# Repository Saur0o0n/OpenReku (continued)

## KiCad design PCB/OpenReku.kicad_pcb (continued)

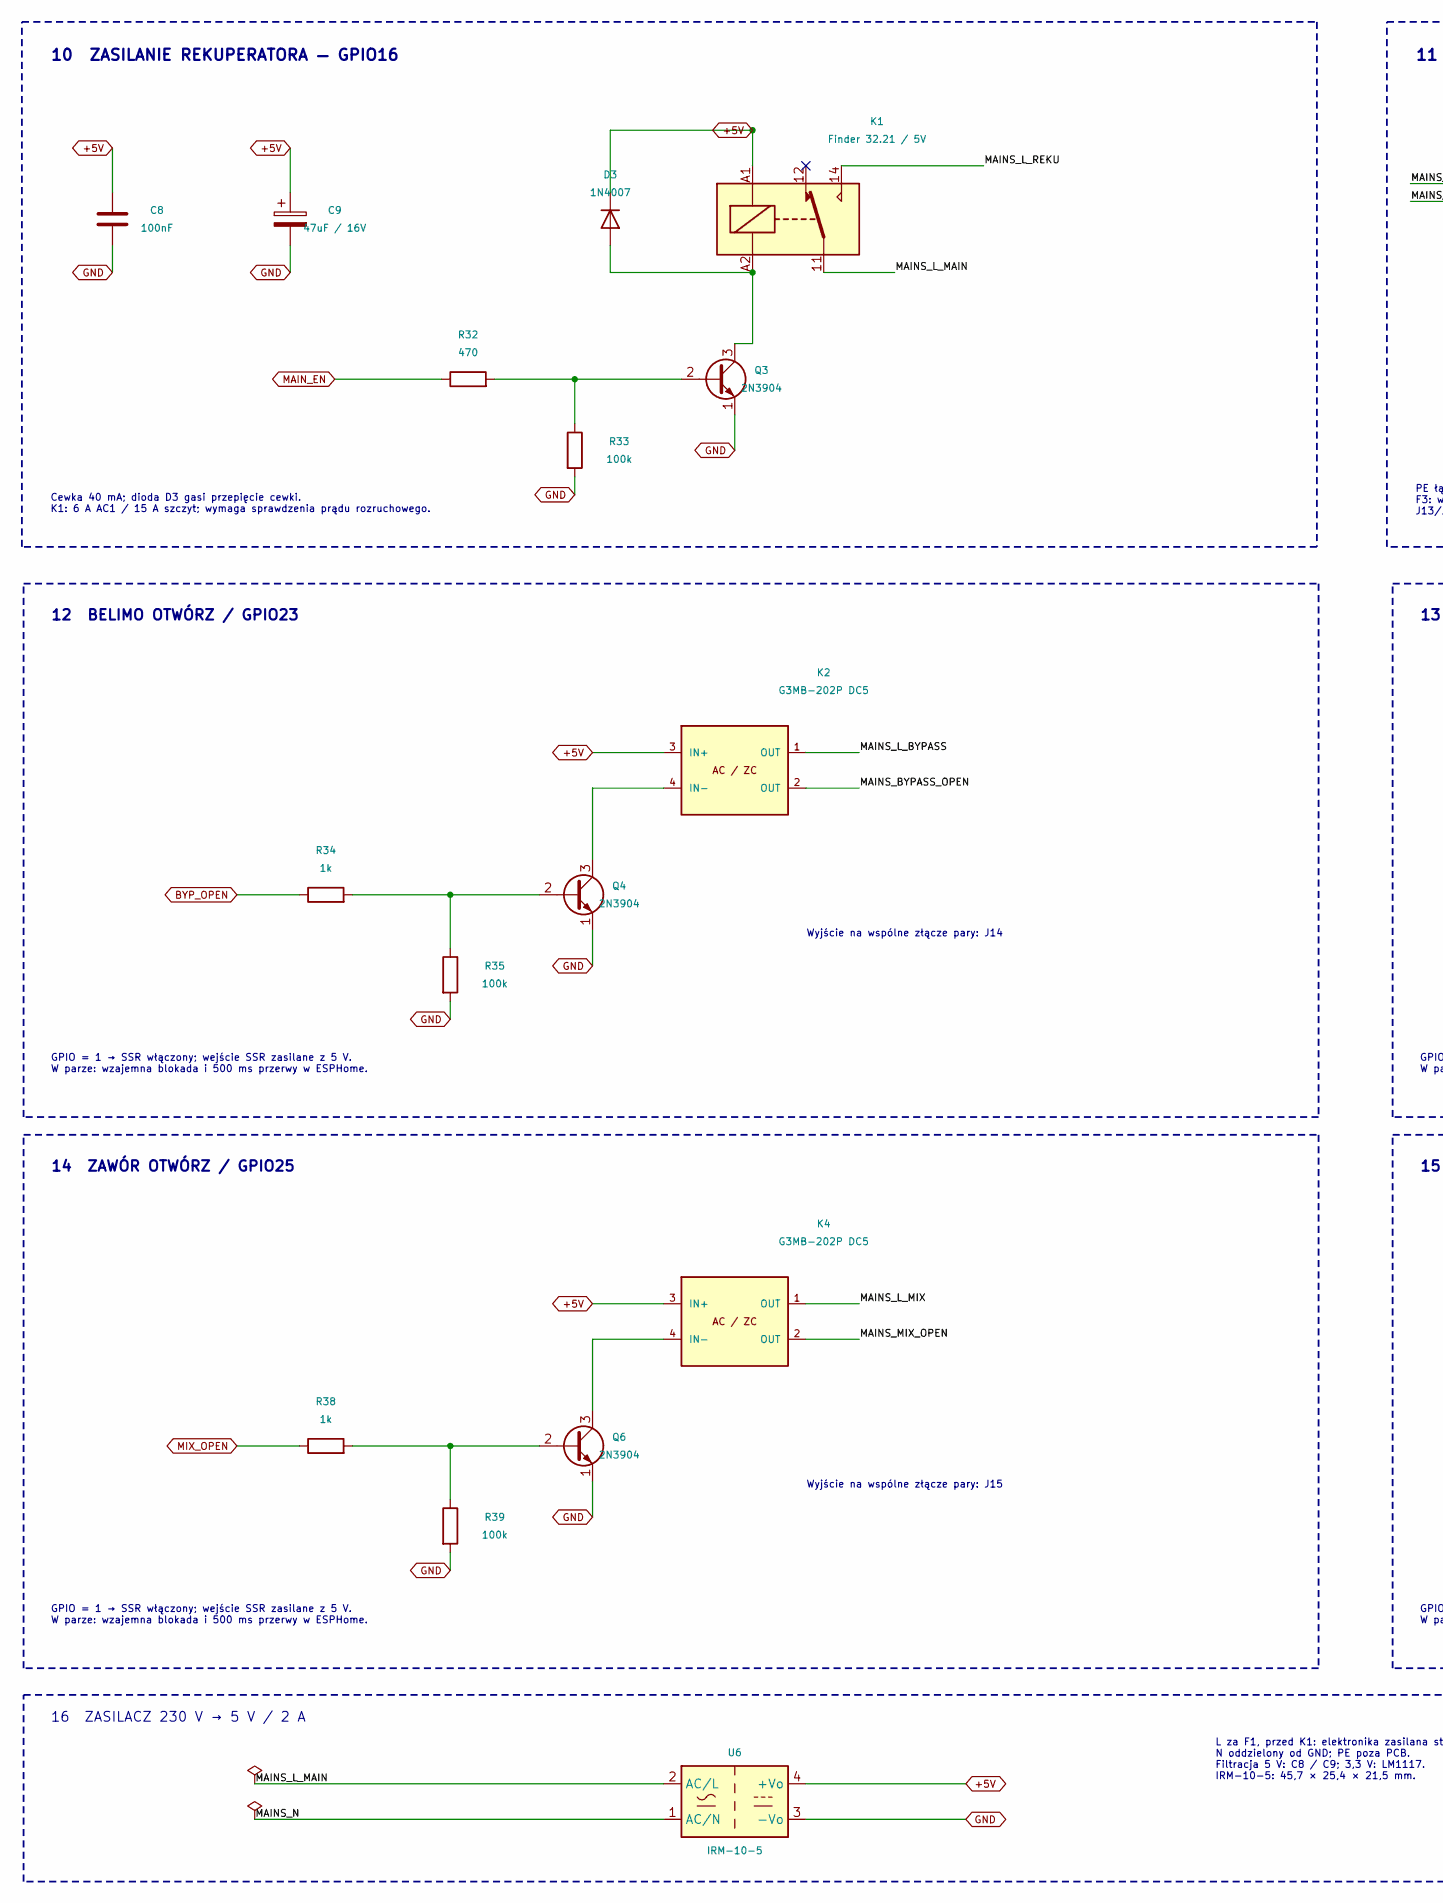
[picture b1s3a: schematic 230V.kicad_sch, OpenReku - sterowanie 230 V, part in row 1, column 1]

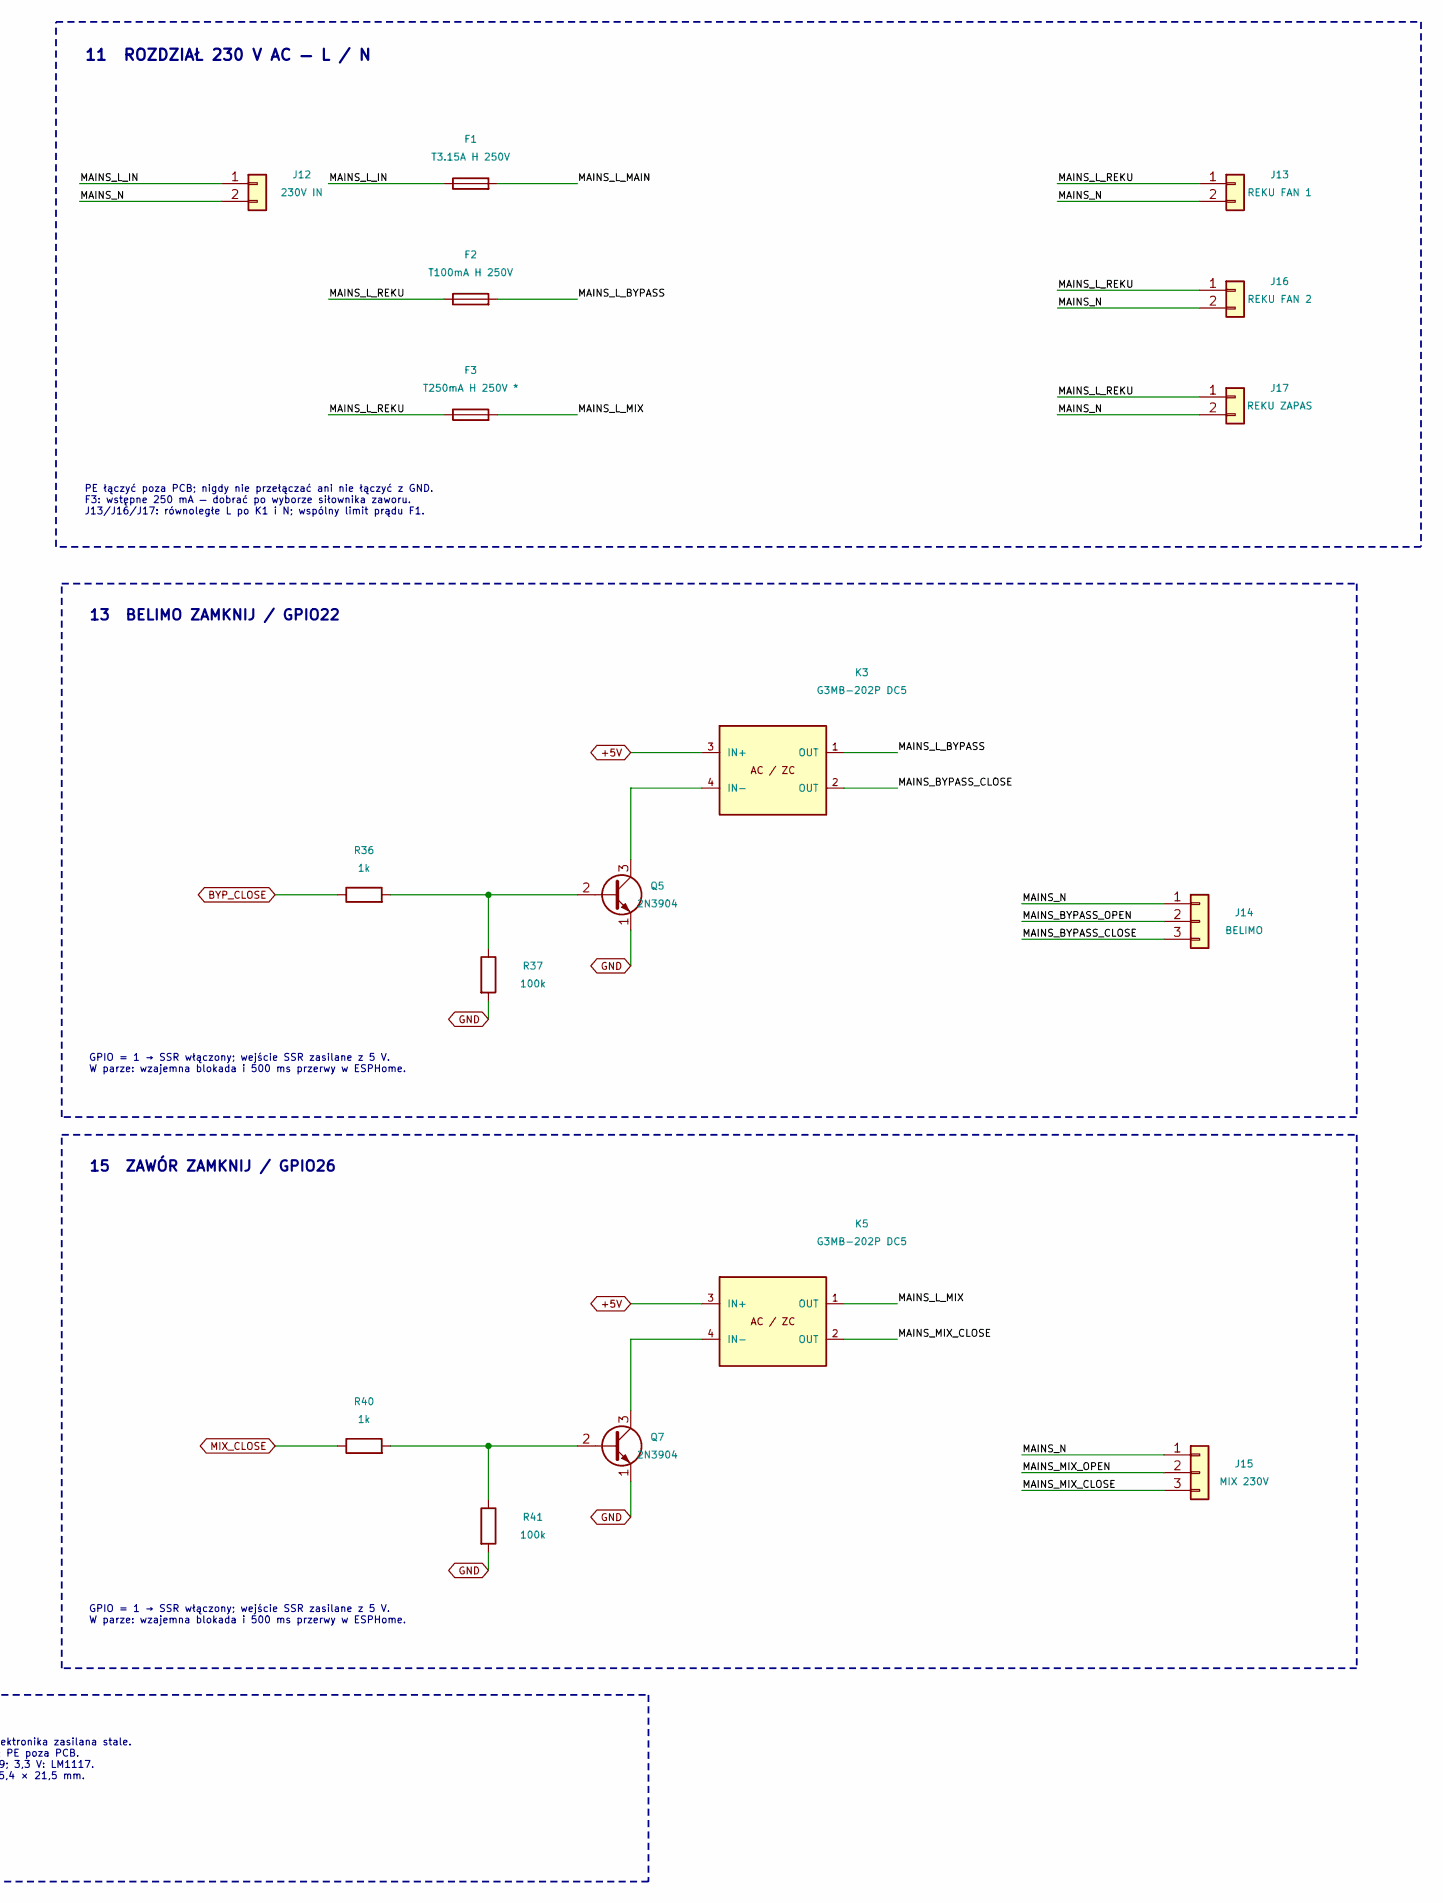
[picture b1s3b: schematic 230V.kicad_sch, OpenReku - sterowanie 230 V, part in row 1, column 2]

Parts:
C8: 100nF; C_1206_3216Metric
C9: 47uF / 16V; CP_Radial_D5.0mm_P2.00mm
D3: 1N4007; D_DO-41_SOD81_P10.16mm_Horizontal
F1: T3.15A H 250V; Fuseholder_Cylinder-5x20mm_Schurter_0031_8201_Horizontal_Op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
F2: T100mA H 250V; Fuseholder_Cylinder-5x20mm_Schurter_0031_8201_Horizontal_Op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
F3: T250mA H 250V *; Fuseholder_Cylinder-5x20mm_Schurter_0031_8201_Horizontal_Op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
J12: 230V IN; PhoenixContact_MSTBA_2,5_2-G-5,08_1x02_P5.08mm_Horizontal_E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; MPN 1757242
J13: REKU FAN 1; PhoenixContact_MSTBA_2,5_2-G-5,08_1x02_P5.08mm_Horizontal_E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; MPN 1757242
J14: BELIMO; PhoenixContact_MSTBA_2,5_3-G-5,08_1x03_P5.08mm_Horizontal_E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; MPN 1757255
J15: MIX 230V; PhoenixContact_MSTBA_2,5_3-G-5,08_1x03_P5.08mm_Horizontal_E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; MPN 1757255
J16: REKU FAN 2; PhoenixContact_MSTBA_2,5_2-G-5,08_1x02_P5.08mm_Horizontal_E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; MPN 1757242
J17: REKU ZAPAS; PhoenixContact_MSTBA_2,5_2-G-5,08_1x02_P5.08mm_Horizontal_E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; MPN 1757242
K1: Finder 32.21 / 5V; Relay_SPDT_Finder_32.21-x000; MPN 32.21.7.005.4000
K2, K3, K4, K5: G3MB-202P DC5; Omron_G3MB-202P_SIP4; MPN G3MB-202P DC5
Q3, Q4, Q5, Q6, Q7: 2N3904; TO-92_Inline
R32: 470; R_1206_3216Metric
R33, R35, R37, R39, R41: 100k; R_1206_3216Metric
R34, R36, R38, R40: 1k; R_1206_3216Metric
U6: IRM-10-5; Converter_ACDC_MeanWell_IRM-10-xx_THT

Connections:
+5V: C8.1, C9.1, D3.1 (K), K1.A1, K2.3 (IN+), K3.3 (IN+), K4.3 (IN+), K5.3 (IN+), U6.4 (+Vo); also elsewhere on the board
/230V/MAINS_BYPASS_CLOSE: J14.3, K3.2 (OUT)
/230V/MAINS_BYPASS_OPEN: J14.2, K2.2 (OUT)
/230V/MAINS_L_BYPASS: F2.2, K2.1 (OUT), K3.1 (OUT)
/230V/MAINS_L_IN: F1.1, J12.1
/230V/MAINS_L_MAIN: F1.2, K1.11, U6.2 (AC/L)
/230V/MAINS_L_MIX: F3.2, K4.1 (OUT), K5.1 (OUT)
/230V/MAINS_L_REKU: F2.1, F3.1, J13.1, J16.1, J17.1, K1.14
/230V/MAINS_MIX_CLOSE: J15.3, K5.2 (OUT)
/230V/MAINS_MIX_OPEN: J15.2, K4.2 (OUT)
/230V/MAINS_N: J12.2, J13.2, J14.1, J15.1, J16.2, J17.2, U6.1 (AC/N)
BYP_CLOSE: R36.1; also elsewhere on the board
BYP_OPEN: R34.1; also elsewhere on the board
GND: C8.2, C9.2, Q3.1 (E), Q4.1 (E), Q5.1 (E), Q6.1 (E), Q7.1 (E), R33.2, R35.2, R37.2, R39.2, R41.2, U6.3 (-Vo); also elsewhere on the board
MAIN_EN: R32.1; also elsewhere on the board
MIX_CLOSE: R40.1; also elsewhere on the board
MIX_OPEN: R38.1; also elsewhere on the board
unnamed: D3.2 (A), K1.A2, Q3.3 (C)
unnamed: K2.4 (IN-), Q4.3 (C)
unnamed: K3.4 (IN-), Q5.3 (C)
unnamed: K4.4 (IN-), Q6.3 (C)
unnamed: K5.4 (IN-), Q7.3 (C)
unnamed: Q3.2 (B), R32.2, R33.1
unnamed: Q4.2 (B), R34.2, R35.1
unnamed: Q5.2 (B), R36.2, R37.1
unnamed: Q6.2 (B), R38.2, R39.1
unnamed: Q7.2 (B), R40.2, R41.1

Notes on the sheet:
10 ZASILANIE REKUPERATORA — GPIO16
Cewka 40 mA; dioda D3 gasi przepięcie cewki. K1: 6 A AC1 / 15 A szczyt; wymaga sprawdzenia prądu rozruchowego.
11 ROZDZIAŁ 230 V AC — L / N
PE łączyć poza PCB; nigdy nie przełączać ani nie łączyć z GND. F3: wstępne 250 mA — dobrać po wyborze siłownika zaworu. J13/J16/J17: równoległe L po K1 i N; wspólny limit prądu F1.
12 BELIMO OTWÓRZ / GPIO23
Wyjście na wspólne złącze pary: J14
GPIO = 1 → SSR włączony; wejście SSR zasilane z 5 V. W parze: wzajemna blokada i 500 ms przerwy w ESPHome.
13 BELIMO ZAMKNIJ / GPIO22
14 ZAWÓR OTWÓRZ / GPIO25
Wyjście na wspólne złącze pary: J15
15 ZAWÓR ZAMKNIJ / GPIO26
16 ZASILACZ 230 V → 5 V / 2 A
L za F1, przed K1: elektronika zasilana stale. N oddzielony od GND; PE poza PCB. Filtracja 5 V: C8 / C9; 3,3 V: LM1117. IRM-10-5: 45,7 × 25,4 × 21,5 mm.

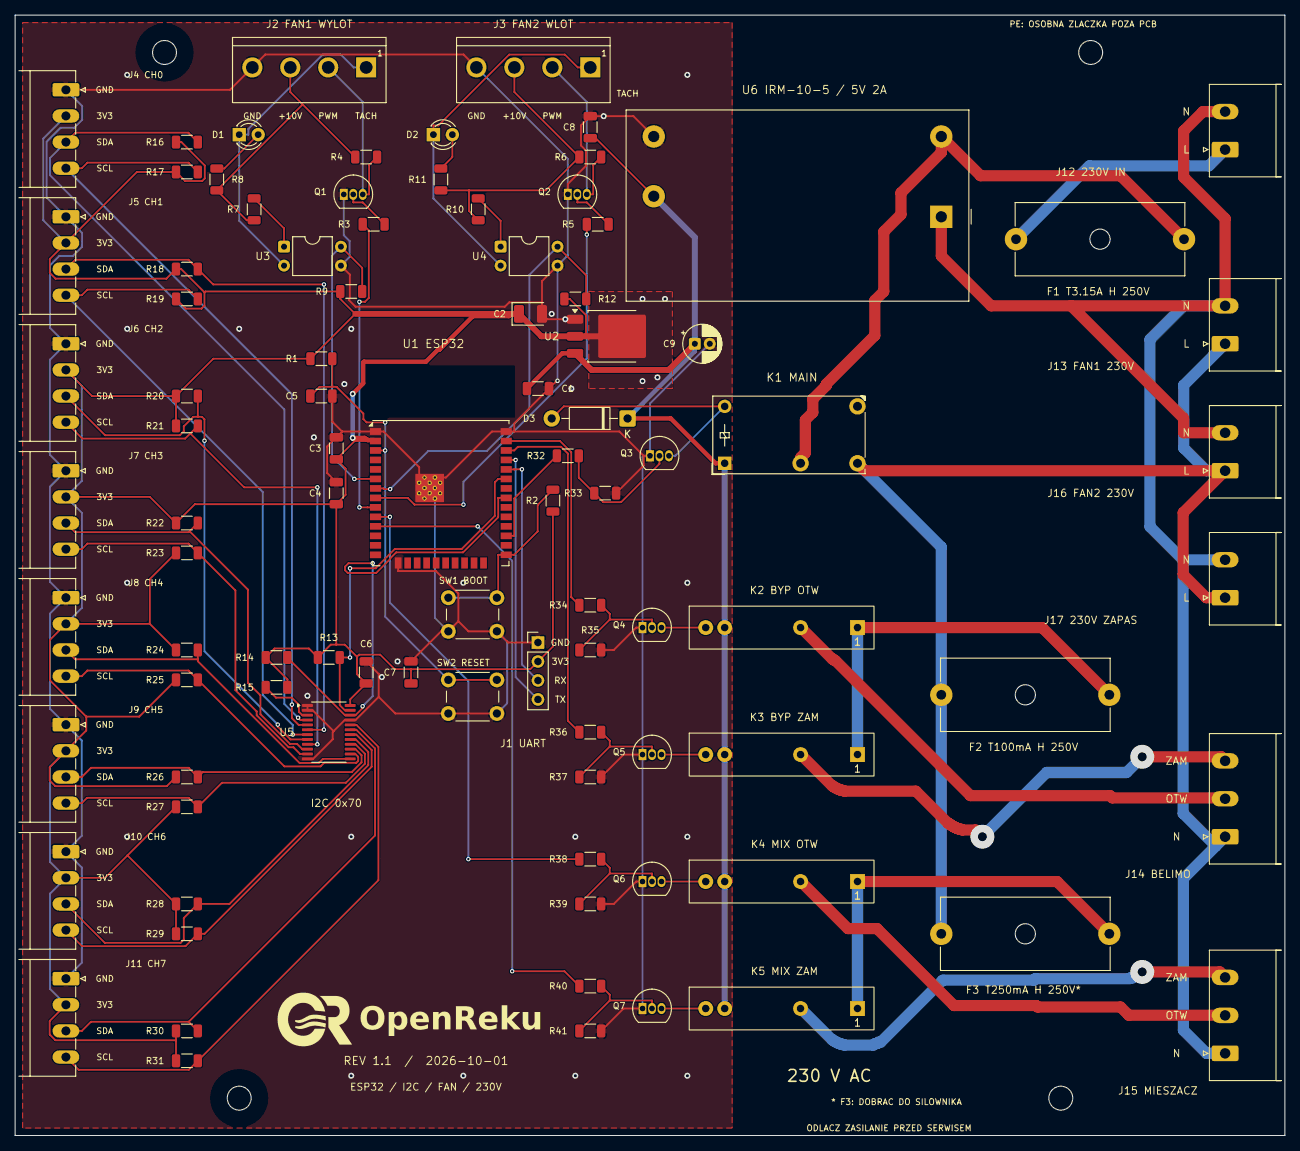
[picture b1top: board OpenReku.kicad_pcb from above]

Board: 2 copper layers, 170.0 x 150.0 mm, 98 parts (0 on the bottom side), 67 nets.

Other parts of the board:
H1, H2, H3, H4: MountingHole_3.2mm_M3
LOGO1: OpenReku logo; Logo_OpenReku_36mm

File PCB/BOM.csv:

"Reference","Quantity","Value","Footprint","MPN","MatingConnector","Pinout","AssemblyNote","DNP","Datasheet"
"C1","1","10uF / 16V X7R","Capacitor_SMD:C_1206_3216Metric","","","","","",""
"C2","1","22uF / 10V Ta","Capacitor_Tantalum_SMD:CP_EIA-3528-21_Kemet-B","","","","","",""
"C3,C6,C8","3","100nF","Capacitor_SMD:C_1206_3216Metric","","","","","",""
"C4","1","10uF","Capacitor_SMD:C_1206_3216Metric","","","","","",""
"C5","1","1uF / 10V X7R","Capacitor_SMD:C_1206_3216Metric","","","","","",""
"C7","1","1uF","Capacitor_SMD:C_1206_3216Metric","","","","","",""
"C9","1","47uF / 16V","Capacitor_THT:CP_Radial_D5.0mm_P2.00mm","","","","","",""
"D1,D2","2","LED RPM","LED_THT:LED_D3.0mm","","","","","",""
"D3","1","1N4007","Diode_THT:D_DO-41_SOD81_P10.16mm_Horizontal","","","","","",""
"F1","1","T3.15A H 250V","Fuse:Fuseholder_Cylinder-5x20mm_Schurter_0031_8201_Horizontal_Open","","","","","",""
"F2","1","T100mA H 250V","Fuse:Fuseholder_Cylinder-5x20mm_Schurter_0031_8201_Horizontal_Open","","","","","",""
"F3","1","T250mA H 250V *","Fuse:Fuseholder_Cylinder-5x20mm_Schurter_0031_8201_Horizontal_Open","","","","","",""
"J1","1","UART 3V3","Connector_PinHeader_2.54mm:PinHeader_1x04_P2.54mm_Vertical","","","","","",""
"J2","1","FAN1 WYLOT","Rekuperator:KLS2-EDV-5.08-04P-4_Vertical","KLS2-EDV-5.08-04P-4","KLS2-EDK-5.08-04P-4S","","","","https://img.klsele.com/admin/product_upload/20250331141523L-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"
"J3","1","FAN2 WLOT","Rekuperator:KLS2-EDV-5.08-04P-4_Vertical","KLS2-EDV-5.08-04P-4","KLS2-EDK-5.08-04P-4S","","","","https://img.klsele.com/admin/product_upload/20250331141523L-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"
"J4","1","CH0 ARK 3.5","Rekuperator:PhoenixContact_MC_1,5_4-G-3.5_1x04_P3.50mm_Horizontal_Edge","1844236","Phoenix Contact 1840382 / MC 1,5/4-ST-3,5","1 GND; 2 +3V3; 3 SDA; 4 SCL","","",""
"J5","1","CH1 ARK 3.5","Rekuperator:PhoenixContact_MC_1,5_4-G-3.5_1x04_P3.50mm_Horizontal_Edge","1844236","Phoenix Contact 1840382 / MC 1,5/4-ST-3,5","1 GND; 2 +3V3; 3 SDA; 4 SCL","","",""
"J6","1","CH2 ARK 3.5","Rekuperator:PhoenixContact_MC_1,5_4-G-3.5_1x04_P3.50mm_Horizontal_Edge","1844236","Phoenix Contact 1840382 / MC 1,5/4-ST-3,5","1 GND; 2 +3V3; 3 SDA; 4 SCL","","",""
"J7","1","CH3 ARK 3.5","Rekuperator:PhoenixContact_MC_1,5_4-G-3.5_1x04_P3.50mm_Horizontal_Edge","1844236","Phoenix Contact 1840382 / MC 1,5/4-ST-3,5","1 GND; 2 +3V3; 3 SDA; 4 SCL","","",""
"J8","1","CH4 ARK 3.5","Rekuperator:PhoenixContact_MC_1,5_4-G-3.5_1x04_P3.50mm_Horizontal_Edge","1844236","Phoenix Contact 1840382 / MC 1,5/4-ST-3,5","1 GND; 2 +3V3; 3 SDA; 4 SCL","","",""
"J9","1","CH5 ARK 3.5","Rekuperator:PhoenixContact_MC_1,5_4-G-3.5_1x04_P3.50mm_Horizontal_Edge","1844236","Phoenix Contact 1840382 / MC 1,5/4-ST-3,5","1 GND; 2 +3V3; 3 SDA; 4 SCL","","",""
"J10","1","CH6 ARK 3.5","Rekuperator:PhoenixContact_MC_1,5_4-G-3.5_1x04_P3.50mm_Horizontal_Edge","1844236","Phoenix Contact 1840382 / MC 1,5/4-ST-3,5","1 GND; 2 +3V3; 3 SDA; 4 SCL","","",""
"J11","1","CH7 ARK 3.5","Rekuperator:PhoenixContact_MC_1,5_4-G-3.5_1x04_P3.50mm_Horizontal_Edge","1844236","Phoenix Contact 1840382 / MC 1,5/4-ST-3,5","1 GND; 2 +3V3; 3 SDA; 4 SCL","","",""
"J12","1","230V IN","Rekuperator:PhoenixContact_MSTBA_2,5_2-G-5,08_1x02_P5.08mm_Horizontal_Edge","1757242","MSTB 2,5/2-ST-5,08","1 MAINS_L_IN; 2 MAINS_N","","",""
"J13","1","REKU FAN 1","Rekuperator:PhoenixContact_MSTBA_2,5_2-G-5,08_1x02_P5.08mm_Horizontal_Edge","1757242","MSTB 2,5/2-ST-5,08","1 MAINS_L_REKU; 2 MAINS_N","","",""
"J14","1","BELIMO","Rekuperator:PhoenixContact_MSTBA_2,5_3-G-5,08_1x03_P5.08mm_Horizontal_Edge","1757255","MSTB 2,5/3-ST-5,08","1 MAINS_N; 2 MAINS_BYPASS_OPEN; 3 MAINS_BYPASS_CLOSE","","",""
"J15","1","MIX 230V","Rekuperator:PhoenixContact_MSTBA_2,5_3-G-5,08_1x03_P5.08mm_Horizontal_Edge","1757255","MSTB 2,5/3-ST-5,08","1 MAINS_N; 2 MAINS_MIX_OPEN; 3 MAINS_MIX_CLOSE","","",""
"J16","1","REKU FAN 2","Rekuperator:PhoenixContact_MSTBA_2,5_2-G-5,08_1x02_P5.08mm_Horizontal_Edge","1757242","MSTB 2,5/2-ST-5,08","1 MAINS_L_REKU; 2 MAINS_N","","",""
"J17","1","REKU ZAPAS","Rekuperator:PhoenixContact_MSTBA_2,5_2-G-5,08_1x02_P5.08mm_Horizontal_Edge","1757242","MSTB 2,5/2-ST-5,08","1 MAINS_L_REKU; 2 MAINS_N","","",""
"K1","1","Finder 32.21 / 5V","Relay_THT:Relay_SPDT_Finder_32.21-x000","32.21.7.005.4000","","","6 A AC1; verify recuperator inrush and load category before production","",""
"K2,K3,K4,K5","4","G3MB-202P DC5","Rekuperator:Omron_G3MB-202P_SIP4","G3MB-202P DC5","","","Legacy tested prototype circuit; load current below 100mA is outside manufacturer specification","","https://components101.com/sites/default/files/component_data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"
"Q1,Q2,Q3,Q4,Q5,Q6,Q7","7","2N3904","Package_TO_SOT_THT:TO-92_Inline","","","","","",""
"R1,R2,R4,R6,R15","5","10k","Resistor_SMD:R_1206_3216Metric","","","","","",""
"R3,R5","2","2.2k","Resistor_SMD:R_1206_3216Metric","","","","","",""
"R7,R10","2","1.8k","Resistor_SMD:R_1206_3216Metric","","","","","",""
"R8,R9,R11,R12,R13,R14","6","4.7k","Resistor_SMD:R_1206_3216Metric","","","","","",""
"R16,R17,R18,R19,R20,R21,R22,R23,R24,R25,R26,R27,R28,R29,R30,R31","16","4.7k","Resistor_SMD:R_1206_3216Metric","","","","Omit if sensor module already has adequate pull-up to 3.3 V","",""
"R32","1","470","Resistor_SMD:R_1206_3216Metric","","","","","",""
"R33,R35,R37,R39,R41","5","100k","Resistor_SMD:R_1206_3216Metric","","","","","",""
"R34,R36,R38,R40","4","1k","Resistor_SMD:R_1206_3216Metric","","","","","",""
"SW1","1","BOOT","Button_Switch_THT:SW_PUSH_6mm","","","","","",""
"SW2","1","RESET","Button_Switch_THT:SW_PUSH_6mm","","","","","",""
"U1","1","ESP32-WROOM-32U","Rekuperator:ESP32-WROOM-32U_0.3mm_ThermalDrills","","","","","","https://www.espressif.com/sites/default/files/documentation/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"
"U2","1","LM1117DT-3.3","Package_TO_SOT_SMD:TO-252-3_TabPin2","","","","","","http://www.ti.com/lit/ds/symlink/lm1117.pdf"
"U3,U4","2","PC817","Package_DIP:DIP-4_W7.62mm","","","","","",""
"U5","1","TCA9548APWR","Package_SO:TSSOP-24_4.4x7.8mm_P0.65mm","TCA9548APWR","","","","","https://www.ti.com/lit/ds/symlink/tca9548a.pdf"
"U6","1","IRM-10-5","Converter_ACDC:Converter_ACDC_MeanWell_IRM-10-xx_THT","","","","","",""
